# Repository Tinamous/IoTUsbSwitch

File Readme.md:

IoT USB Switch
--------------

USB Power switch. Control the power to a USB powered device (e.g. light) via an internet connected Particle Photon. 

Also measures current consumption as well as in and out voltages.

Rev1:
-----

Initial version. 3 boards build, appears to work!

Issues:
* PCB was a little too long and needed a small amount removed at the USB plug.
* With headers and a socket the Photon is very tall. It's mounted on the bottom of the board with USB plug and socket on the top which makes it a little odd.
* Photon in headers is about the same height as a Double USB socket, LM3526M-L is a dual output device so Rev2 probably worth making dual output as little extra expence.

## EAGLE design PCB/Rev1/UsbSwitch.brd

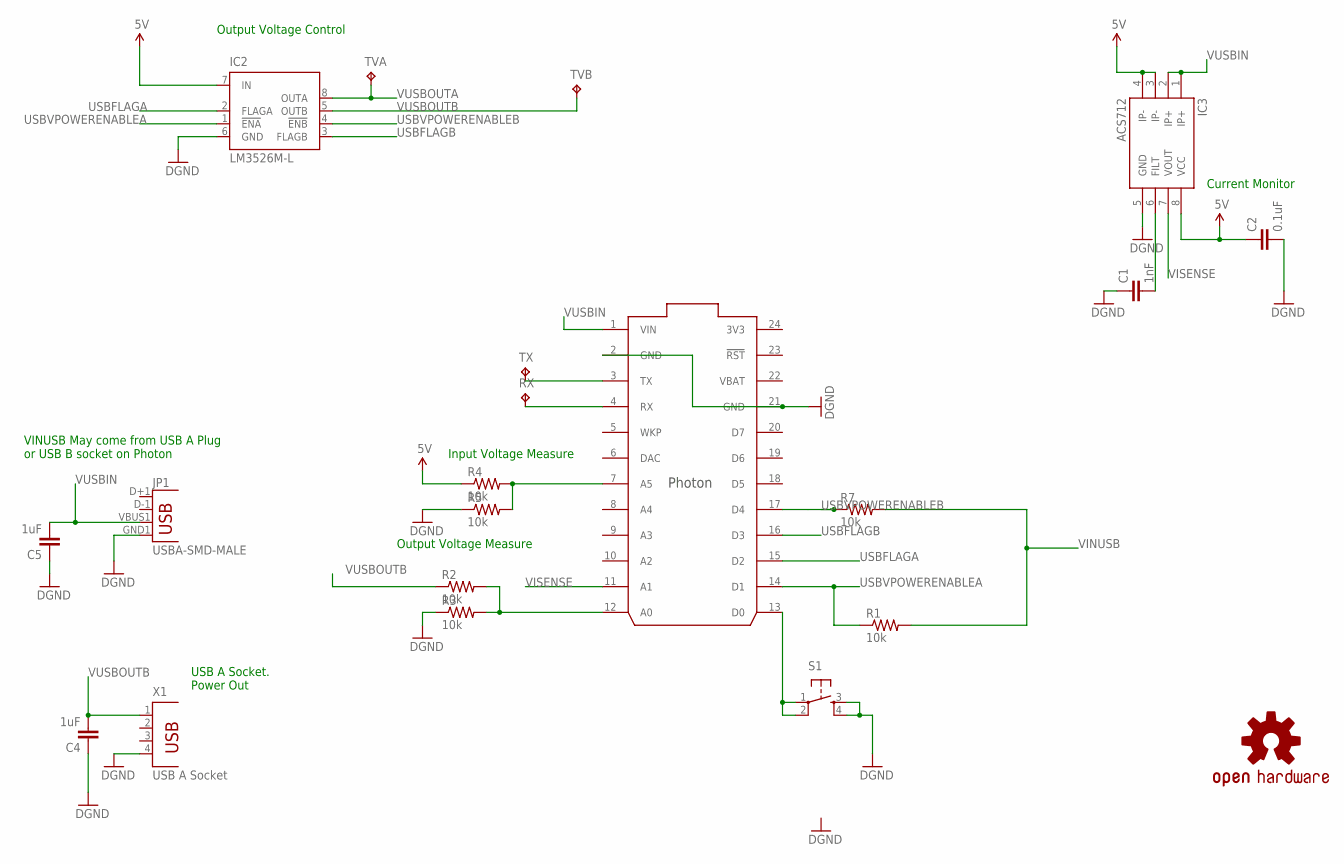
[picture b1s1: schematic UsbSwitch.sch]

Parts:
C1: 1nF; 0805
C2: 0.1uF; 0805
C4, C5: 1uF; 0805
IC1: PHOTON
IC2: LM3526M-L; SO08
IC3: ACS712; SO08
JP1: USBA-SMD-MALE; USB-A-SMT-MALE
LOGO1: OSHW-LOGOM-COPPER; OSHW-LOGO-M_COPPER
R1, R2, R3, R4, R5, R7: 10k; 1206
RX: TPTP20SQ; TP20SQ
S1: TAC_SWITCHSMD; TACTILE_SWITCH_SMD
TVA: TPTP20SQ; TP20SQ
TVB: TPTP20SQ; TP20SQ
TX: TPTP20SQ; TP20SQ
X1: USB A Socket; PN87520

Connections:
3V3: IC1.24 (3V3)
5V: C2.1, IC2.7 (IN), IC3.3 (IP-), IC3.4 (IP-), IC3.8 (VCC), R4.1
GND: C1.1, C2.2, C4.1, C5.1, IC1.2 (GND), IC1.21 (GND), IC2.6 (GND), IC3.5 (GND), JP1.GND1 (GND), R3.1, R5.1, S1.3, S1.4, X1.4
unnamed: IC1.13 (D0), S1.1, S1.2
unnamed: C1.2, IC3.6 (FILT)
unnamed: IC1.3 (TX), TX.TP
unnamed: IC1.4 (RX), RX.TP
unnamed: IC1.12 (A0), R2.2, R3.2
unnamed: IC1.7 (A5), R4.2, R5.2
USBFLAGA: IC1.15 (D2), IC2.2 (FLAGA)
USBFLAGB: IC1.16 (D3), IC2.3 (FLAGB)
USBVPOWERENABLEA: IC1.14 (D1), IC2.1 (!ENA), R1.1
USBVPOWERENABLEB: IC1.17 (D4), IC2.4 (!ENB), R7.1
VBAT: IC1.22 (VBAT)
VINUSB: R1.2, R7.2
VISENSE: IC1.11 (A1), IC3.7 (VOUT)
VUSBIN: C5.2, IC1.1 (VIN), IC3.1 (IP+), IC3.2 (IP+), JP1.VBUS1 (VBUS)
VUSBOUTA: IC2.8 (OUTA), TVA.TP
VUSBOUTB: C4.2, IC2.5 (OUTB), R2.1, TVB.TP, X1.1

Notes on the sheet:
VINUSB May come from USB A Plug or USB B socket on Photon
USB A Socket. Power Out
Output Voltage Measure
Input Voltage Measure
Output Voltage Control
Current Monitor

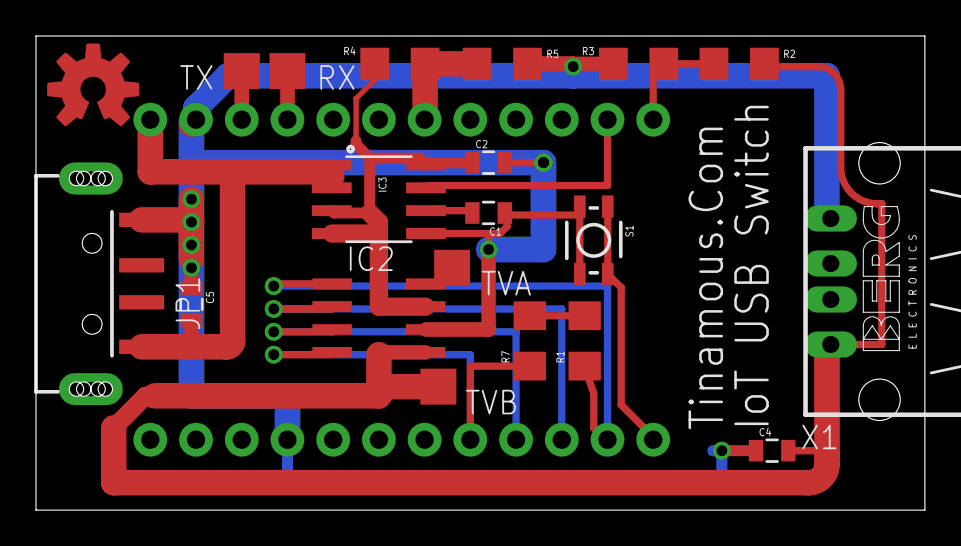
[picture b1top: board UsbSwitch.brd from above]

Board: 2 copper layers, 49.4 x 26.3 mm, 21 parts (1 on the bottom side), 17 nets.

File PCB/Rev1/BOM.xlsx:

| Part | Value | Supplier | Supplier Code | Mfg Code | Note
 | IC3 | ACS712 |  |  |  | Current Monitor
 | IC2 | LM3526M-L |  |  |  | USB Switch
 | IC1 | Photon | Particle.io | Photon |  | With Headers
 | JP1 |  | Farnell | 1696546 | MC32605 | USB Plug - SMD
 | JP2 |  | Farnell | ? |  | USB Socket - Through Hole
 | C1 | 1nf-100nF |  |  |  | 805
 | C2 | 0.1uF |  |  |  | 805
 | C3 | Missing
 | C4 | 1uF
 | C5 | 1uF
 | R1 | 10k |  |  |  | 1206
 | R2 | 10k |  |  |  | 1206
 | R3 | 10k |  |  |  | 1206
 | R3 | 10k |  |  |  | 1206
 | R5 | 10k |  |  |  | 1206
 | R6 | Missing
 | R7 | 10k |  |  |  | 1206
 | S1 |  |  |  |  | Optional

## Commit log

2015-09-05 Added initial revision of the design + PCB
2015-09-05 Added readme
2015-09-05 Added firmware.

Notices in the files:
parts and their libraries:
SparkFun-Connectors: Licensing: Creative Commons ShareAlike 4.0 International - https://creativecommons.org/licenses/by-sa/4.0
